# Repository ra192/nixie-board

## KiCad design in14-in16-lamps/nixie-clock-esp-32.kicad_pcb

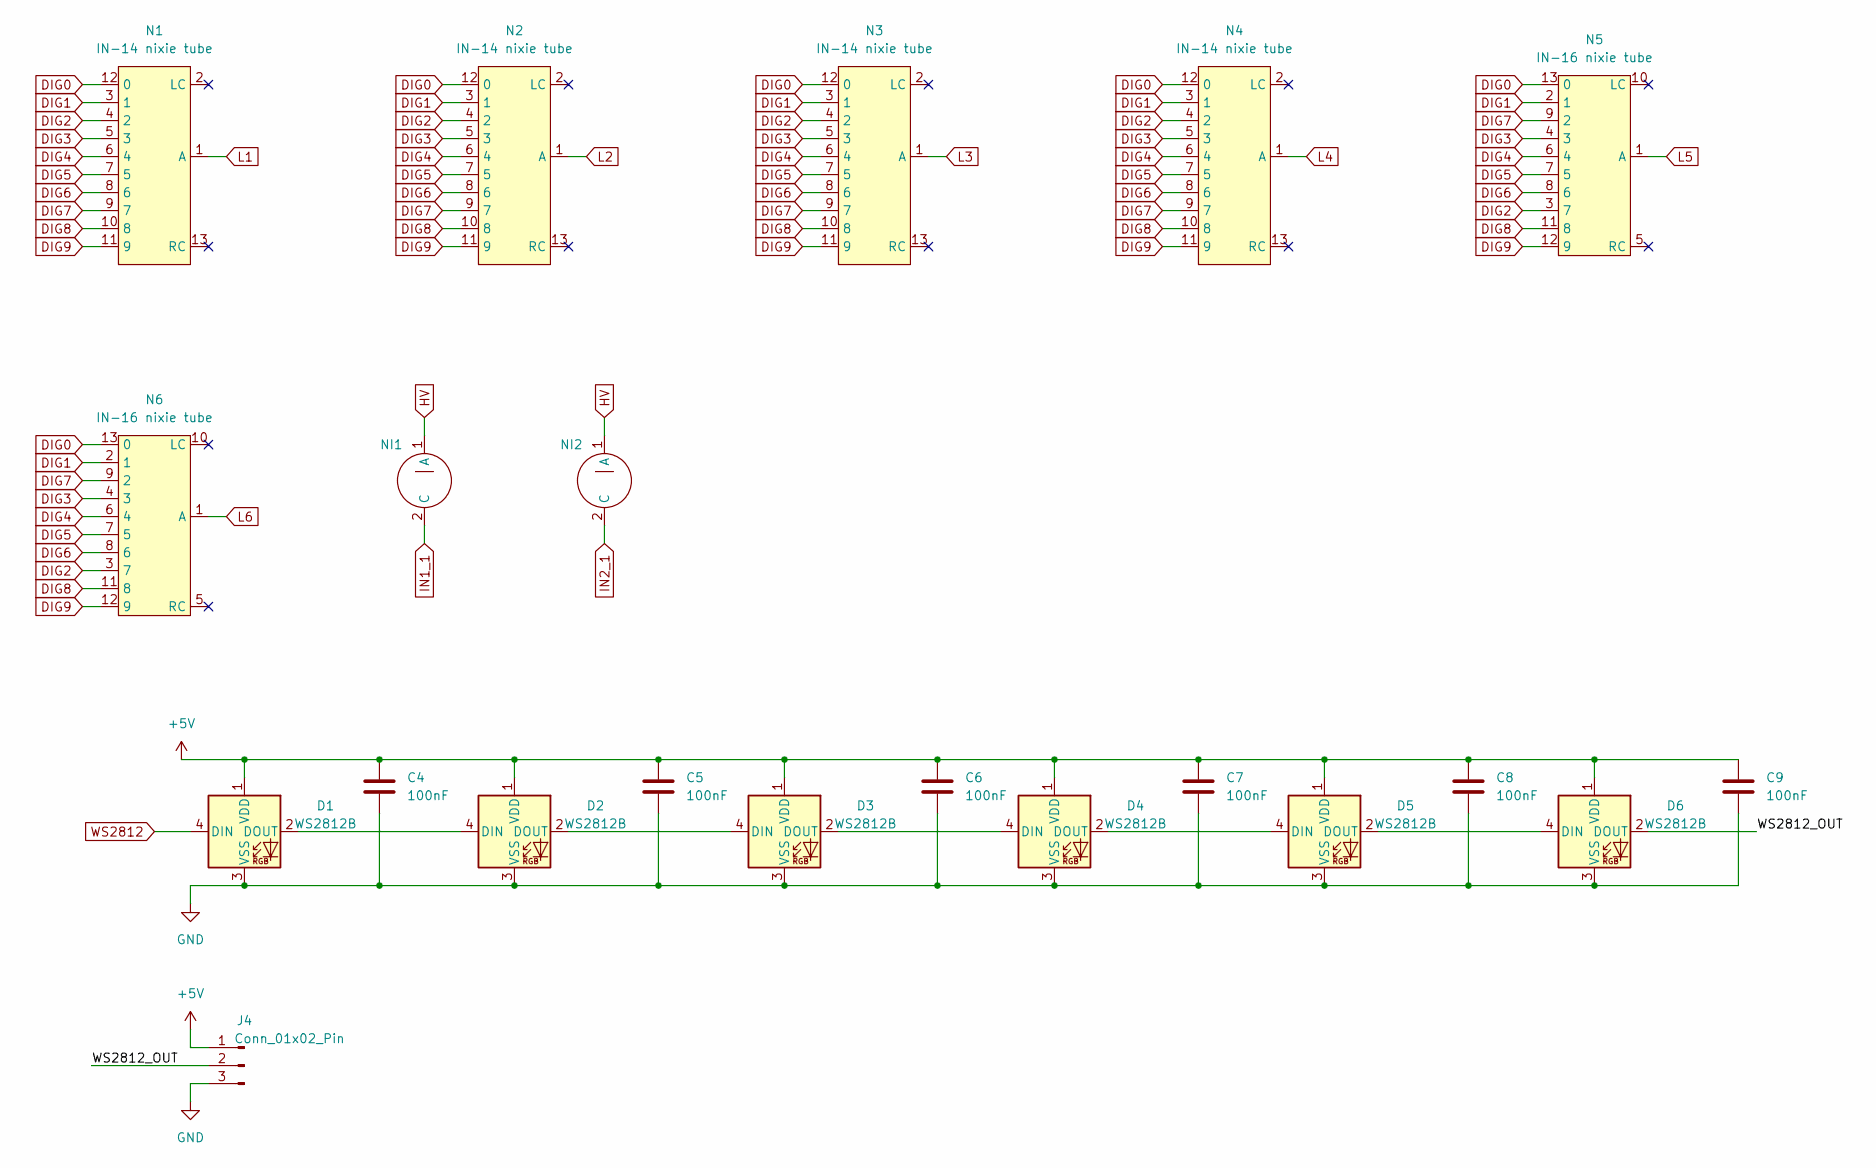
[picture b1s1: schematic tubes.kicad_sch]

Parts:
C4, C5, C6, C7, C8, C9: 100nF; C_0805_2012Metric_Pad1.18x1.45mm_HandSolder
D1, D2, D3, D4, D5, D6: WS2812B; SK6812_mini
J4: Conn_01x02_Pin; PinHeader_1x03_P2.54mm_Vertical
N1, N2, N3, N4: IN-14 nixie tube; IN-14_nixie_tube
N5, N6: IN-16 nixie tube; IN-16_nixie_tube
NI1, NI2: IN-3_indicator

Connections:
+5V: C4.1, C5.1, C6.1, C7.1, C8.1, C9.1, D1.1 (VDD), D2.1 (VDD), D3.1 (VDD), D4.1 (VDD), D5.1 (VDD), D6.1 (VDD), J4.1; also elsewhere on the board
/tubes/WS2812_OUT: D6.2 (DOUT), J4.2
DIG0: N1.12 (0), N2.12 (0), N3.12 (0), N4.12 (0), N5.13 (0), N6.13 (0); also elsewhere on the board
DIG1: N1.3 (1), N2.3 (1), N3.3 (1), N4.3 (1), N5.2 (1), N6.2 (1); also elsewhere on the board
DIG2: N1.4 (2), N2.4 (2), N3.4 (2), N4.4 (2), N5.3 (7), N6.3 (7); also elsewhere on the board
DIG3: N1.5 (3), N2.5 (3), N3.5 (3), N4.5 (3), N5.4 (3), N6.4 (3); also elsewhere on the board
DIG4: N1.6 (4), N2.6 (4), N3.6 (4), N4.6 (4), N5.6 (4), N6.6 (4); also elsewhere on the board
DIG5: N1.7 (5), N2.7 (5), N3.7 (5), N4.7 (5), N5.7 (5), N6.7 (5); also elsewhere on the board
DIG6: N1.8 (6), N2.8 (6), N3.8 (6), N4.8 (6), N5.8 (6), N6.8 (6); also elsewhere on the board
DIG7: N1.9 (7), N2.9 (7), N3.9 (7), N4.9 (7), N5.9 (2), N6.9 (2); also elsewhere on the board
DIG8: N1.10 (8), N2.10 (8), N3.10 (8), N4.10 (8), N5.11 (8), N6.11 (8); also elsewhere on the board
DIG9: N1.11 (9), N2.11 (9), N3.11 (9), N4.11 (9), N5.12 (9), N6.12 (9); also elsewhere on the board
GND: C4.2, C5.2, C6.2, C7.2, C8.2, C9.2, D1.3 (VSS), D2.3 (VSS), D3.3 (VSS), D4.3 (VSS), D5.3 (VSS), D6.3 (VSS), J4.3; also elsewhere on the board
HV: NI1.1 (A), NI2.1 (A); also elsewhere on the board
IN1_1: NI1.2 (C); also elsewhere on the board
IN2_1: NI2.2 (C); also elsewhere on the board
L1: N1.1 (A); also elsewhere on the board
L2: N2.1 (A); also elsewhere on the board
L3: N3.1 (A); also elsewhere on the board
L4: N4.1 (A); also elsewhere on the board
L5: N5.1 (A); also elsewhere on the board
L6: N6.1 (A); also elsewhere on the board
unnamed: D1.2 (DOUT), D2.4 (DIN)
unnamed: D2.2 (DOUT), D3.4 (DIN)
unnamed: D3.2 (DOUT), D4.4 (DIN)
unnamed: D4.2 (DOUT), D5.4 (DIN)
unnamed: D5.2 (DOUT), D6.4 (DIN)
WS2812: D1.4 (DIN); also elsewhere on the board

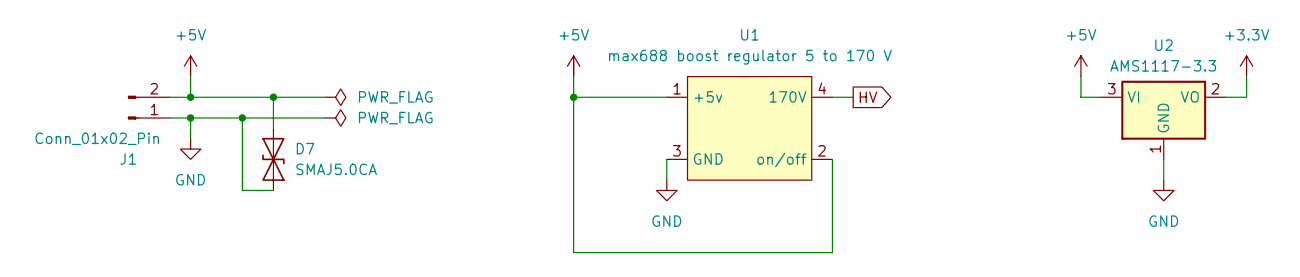
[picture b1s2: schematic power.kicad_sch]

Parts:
D7: SMAJ5.0CA; D_SMA
J1: Conn_01x02_Pin; JST_EH_B2B-EH-A_1x02_P2.50mm_Vertical
U1: max688 boost regulator 5 to 170 V; max668_boost_regulator
U2: AMS1117-3.3; SOT-223-3_TabPin2

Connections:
+3.3V: U2.2 (VO); also elsewhere on the board
+5V: D7.2 (A2), J1.2, U1.1 (+5v), U1.2 (on/off), U2.3 (VI); also elsewhere on the board
GND: D7.1 (A1), J1.1, U1.3 (GND), U2.1 (GND); also elsewhere on the board
HV: U1.4 (170V); also elsewhere on the board

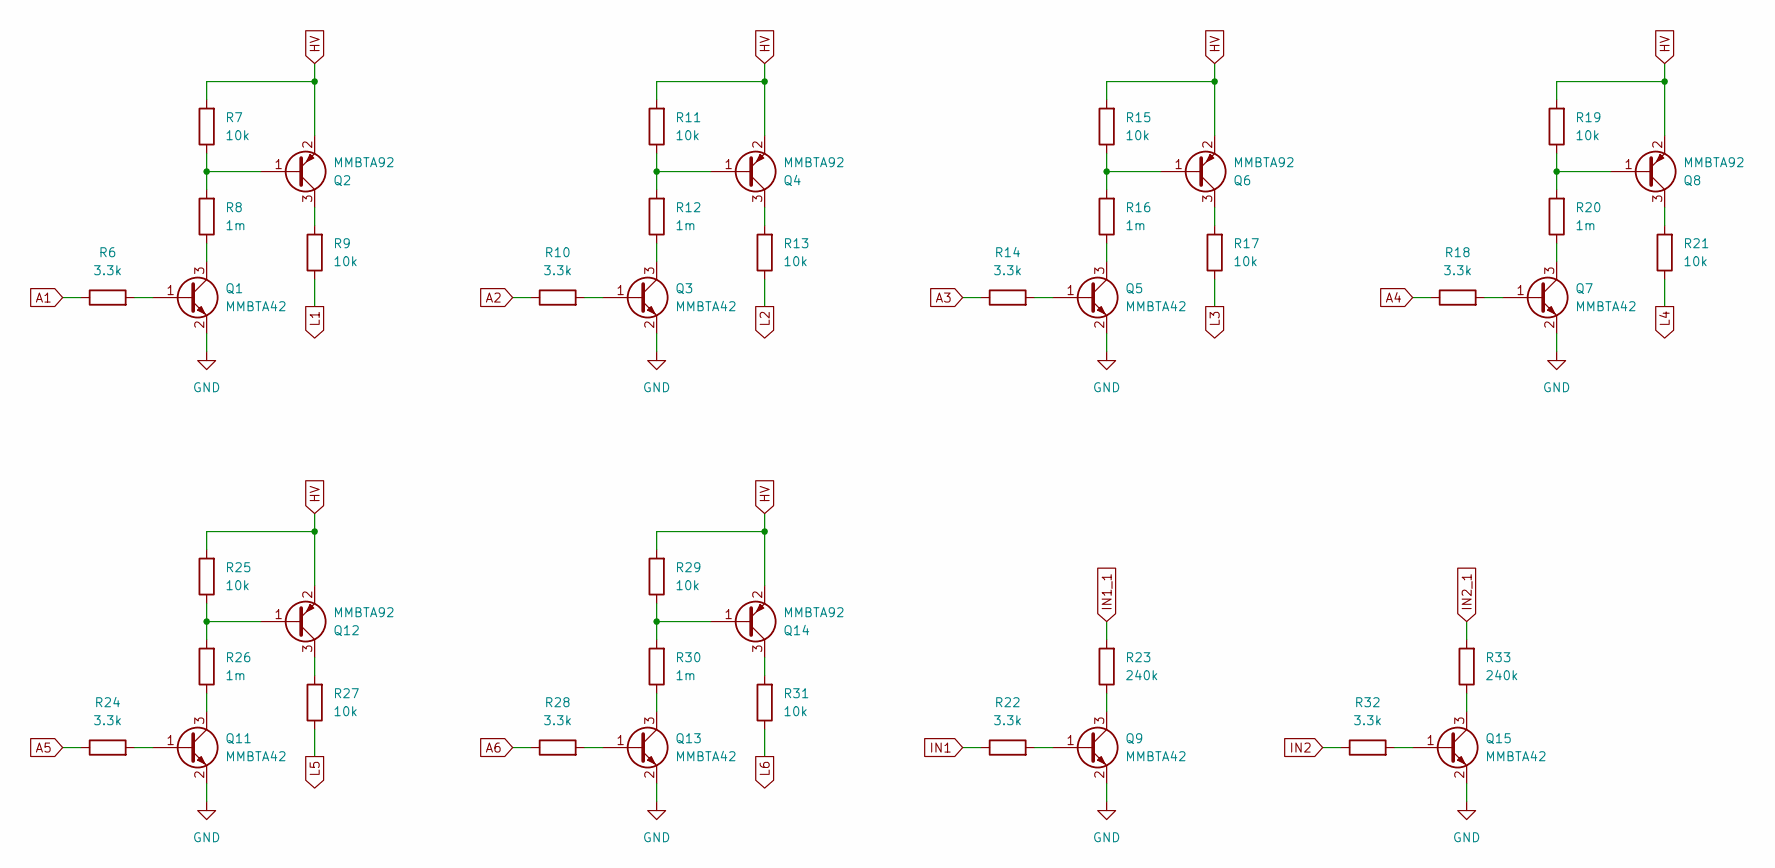
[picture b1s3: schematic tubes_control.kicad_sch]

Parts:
Q1, Q3, Q5, Q7, Q9, Q11, Q13, Q15: MMBTA42; SOT-23
Q2, Q4, Q6, Q8, Q12, Q14: MMBTA92; SOT-23
R6, R10, R14, R18, R22, R24, R28, R32: 3.3k; R_0805_2012Metric_Pad1.20x1.40mm_HandSolder
R7, R9, R11, R13, R15, R17, R19, R21, R25, R27, R29, R31: 10k; R_0805_2012Metric_Pad1.20x1.40mm_HandSolder
R8, R12, R16, R20, R26, R30: 1m; R_0805_2012Metric_Pad1.20x1.40mm_HandSolder
R23, R33: 240k; R_0805_2012Metric_Pad1.20x1.40mm_HandSolder

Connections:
A1: R6.1; also elsewhere on the board
A2: R10.1; also elsewhere on the board
A3: R14.1; also elsewhere on the board
A4: R18.1; also elsewhere on the board
A5: R24.1; also elsewhere on the board
A6: R28.1; also elsewhere on the board
GND: Q1.2 (E), Q3.2 (E), Q5.2 (E), Q7.2 (E), Q9.2 (E), Q11.2 (E), Q13.2 (E), Q15.2 (E); also elsewhere on the board
HV: Q2.2 (E), Q4.2 (E), Q6.2 (E), Q8.2 (E), Q12.2 (E), Q14.2 (E), R7.2, R11.2, R15.2, R19.2, R25.2, R29.2; also elsewhere on the board
IN1: R22.1; also elsewhere on the board
IN1_1: R23.2; also elsewhere on the board
IN2: R32.1; also elsewhere on the board
IN2_1: R33.2; also elsewhere on the board
L1: R9.1; also elsewhere on the board
L2: R13.1; also elsewhere on the board
L3: R17.1; also elsewhere on the board
L4: R21.1; also elsewhere on the board
L5: R27.1; also elsewhere on the board
L6: R31.1; also elsewhere on the board
unnamed: Q1.1 (B), R6.2
unnamed: Q1.3 (C), R8.1
unnamed: Q2.1 (B), R7.1, R8.2
unnamed: Q2.3 (C), R9.2
unnamed: Q3.1 (B), R10.2
unnamed: Q3.3 (C), R12.1
unnamed: Q4.1 (B), R11.1, R12.2
unnamed: Q4.3 (C), R13.2
unnamed: Q5.1 (B), R14.2
unnamed: Q5.3 (C), R16.1
unnamed: Q6.1 (B), R15.1, R16.2
unnamed: Q6.3 (C), R17.2
unnamed: Q7.1 (B), R18.2
unnamed: Q7.3 (C), R20.1
unnamed: Q8.1 (B), R19.1, R20.2
unnamed: Q8.3 (C), R21.2
unnamed: Q9.1 (B), R22.2
unnamed: Q9.3 (C), R23.1
unnamed: Q11.1 (B), R24.2
unnamed: Q11.3 (C), R26.1
unnamed: Q12.1 (B), R25.1, R26.2
unnamed: Q12.3 (C), R27.2
unnamed: Q13.1 (B), R28.2
unnamed: Q13.3 (C), R30.1
unnamed: Q14.1 (B), R29.1, R30.2
unnamed: Q14.3 (C), R31.2
unnamed: Q15.1 (B), R32.2
unnamed: Q15.3 (C), R33.1

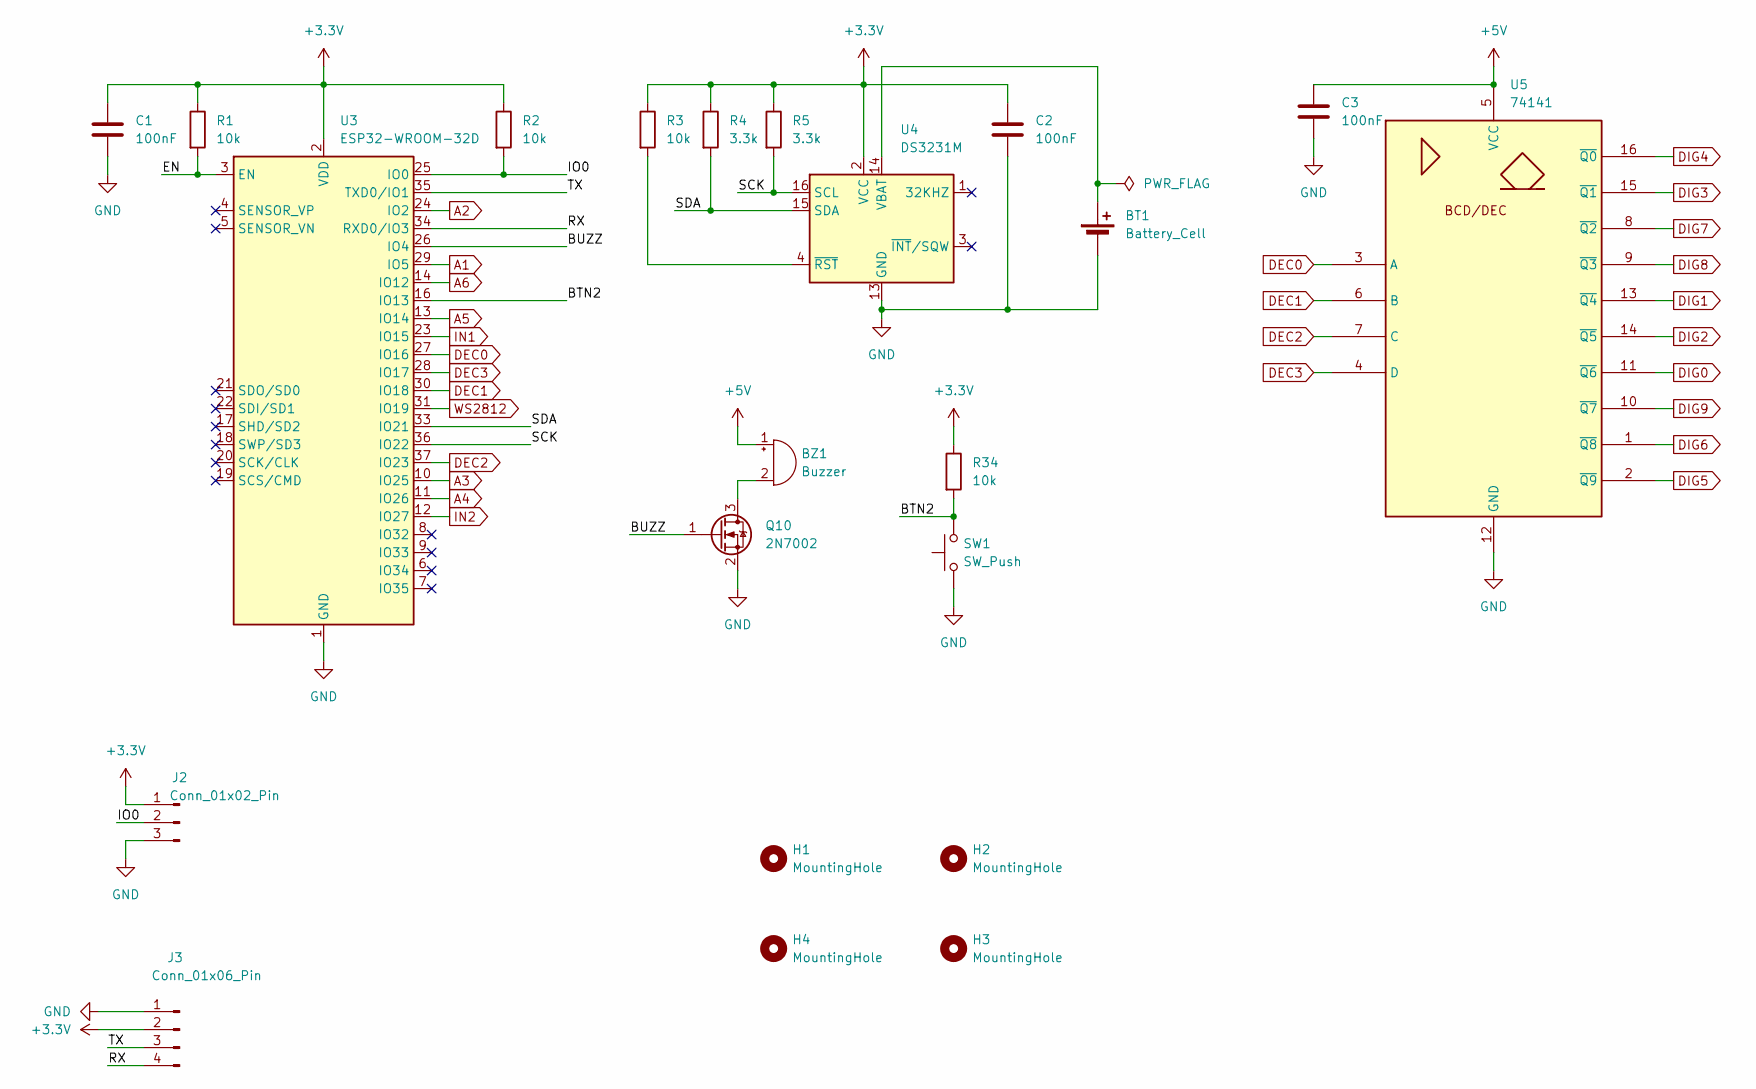
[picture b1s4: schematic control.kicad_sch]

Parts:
BT1: Battery_Cell; CR1220_battery_holder
BZ1: Buzzer; MagneticBuzzer_PUI_AT-0927-TT-6-R
C1, C2, C3: 100nF; C_0805_2012Metric_Pad1.18x1.45mm_HandSolder
H1, H2, H3, H4: MountingHole; MountingHole_3.2mm_M3
J2: Conn_01x02_Pin; PinHeader_1x03_P2.54mm_Vertical
J3: Conn_01x06_Pin; PinHeader_1x04_P2.54mm_Vertical
Q10: 2N7002; SOT-23
R1, R2, R3, R34: 10k; R_0805_2012Metric_Pad1.20x1.40mm_HandSolder
R4, R5: 3.3k; R_0805_2012Metric_Pad1.20x1.40mm_HandSolder
SW1: SW_Push; SW_Push_1P1T_NO_6x6mm_H9.5mm
U3: ESP32-WROOM-32D
U4: DS3231M; SOIC-16W_7.5x10.3mm_P1.27mm
U5: 74141; DIP-16_W7.62mm

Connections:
+3.3V: C1.1, C2.1, J2.1, J3.2, R1.1, R2.1, R3.1, R4.1, R5.1, R34.1, U3.2 (VDD), U4.2 (VCC); also elsewhere on the board
+5V: BZ1.1 (+), C3.1, U5.5 (VCC); also elsewhere on the board
/control/BTN2: R34.2, SW1.2, U3.16 (IO13)
/control/BUZZ: Q10.1 (G), U3.26 (IO4)
/control/EN: R1.2, U3.3 (EN)
/control/IO0: J2.2, R2.2, U3.25 (IO0)
/control/RX: J3.4, U3.34 (RXD0/IO3)
/control/SCK: R5.2, U3.36 (IO22), U4.16 (SCL)
/control/SDA: R4.2, U3.33 (IO21), U4.15 (SDA)
/control/TX: J3.3, U3.35 (TXD0/IO1)
A1: U3.29 (IO5); also elsewhere on the board
A2: U3.24 (IO2); also elsewhere on the board
A3: U3.10 (IO25); also elsewhere on the board
A4: U3.11 (IO26); also elsewhere on the board
A5: U3.13 (IO14); also elsewhere on the board
A6: U3.14 (IO12); also elsewhere on the board
DEC0: U3.27 (IO16), U5.3 (A)
DEC1: U3.30 (IO18), U5.6 (B)
DEC2: U3.37 (IO23), U5.7 (C)
DEC3: U3.28 (IO17), U5.4 (D)
DIG0: U5.11 (~Q6); also elsewhere on the board
DIG1: U5.13 (~Q4); also elsewhere on the board
DIG2: U5.14 (~Q5); also elsewhere on the board
DIG3: U5.15 (~Q1); also elsewhere on the board
DIG4: U5.16 (~Q0); also elsewhere on the board
DIG5: U5.2 (~Q9); also elsewhere on the board
DIG6: U5.1 (~Q8); also elsewhere on the board
DIG7: U5.8 (~Q2); also elsewhere on the board
DIG8: U5.9 (~Q3); also elsewhere on the board
DIG9: U5.10 (~Q7); also elsewhere on the board
GND: BT1.2 (-), C1.2, C2.2, C3.2, J2.3, J3.1, Q10.2 (S), SW1.1, U3.1 (GND), U3.15 (GND), U3.38 (GND), U3.39 (GND), U4.5 (GND), U4.6 (GND), U4.7 (GND), U4.8 (GND), U4.9 (GND), U4.10 (GND), U4.11 (GND), U4.12 (GND), U4.13 (GND), U5.12 (GND); also elsewhere on the board
IN1: U3.23 (IO15); also elsewhere on the board
IN2: U3.12 (IO27); also elsewhere on the board
unnamed: BT1.1 (+), U4.14 (VBAT)
unnamed: BZ1.2 (-), Q10.3 (D)
unnamed: R3.2, U4.4 (~RST)
WS2812: U3.31 (IO19); also elsewhere on the board

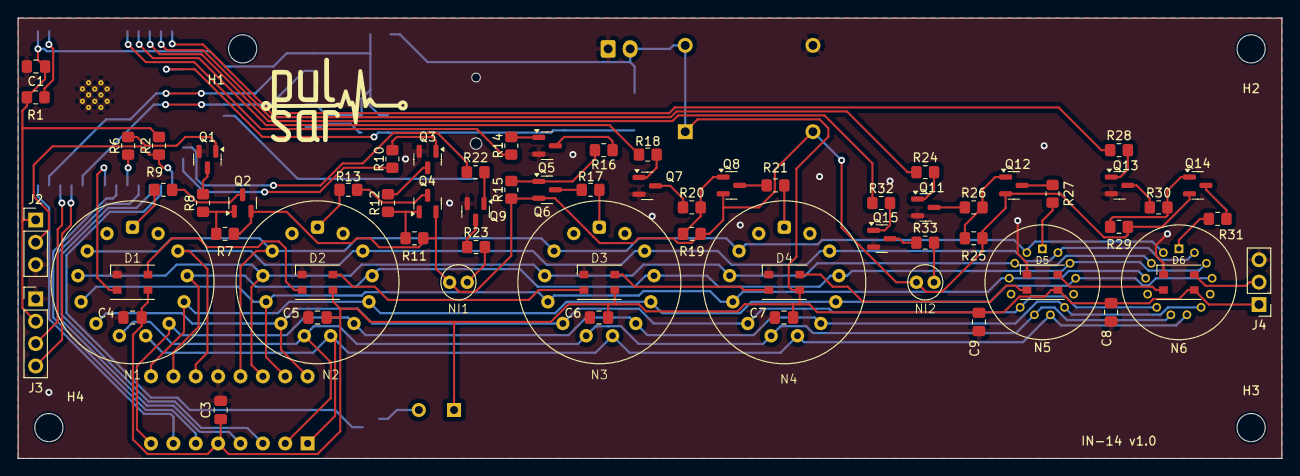
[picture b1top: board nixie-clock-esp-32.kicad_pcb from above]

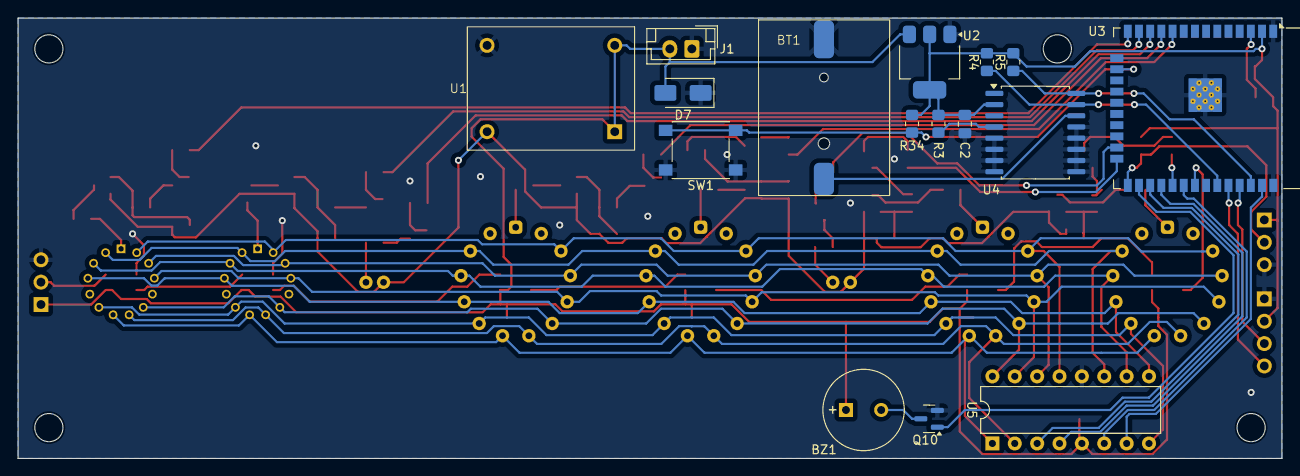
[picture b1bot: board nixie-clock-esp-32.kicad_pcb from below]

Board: 2 copper layers, 143.5 x 50.0 mm, 89 parts (16 on the bottom side), 80 nets.

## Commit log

2024-02-10 add button and ws2812 connector
2024-02-12 rename folder
2024-02-13 change in-14 footprint
2024-02-27 add in-14 and in-16 6 lamp version
2024-03-10 fix i2c pins
2024-03-15 fix i2c connection
